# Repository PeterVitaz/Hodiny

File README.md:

# Hodiny v4.6

Author:     Peter Vitaz
email:      peter@vitaz.tv

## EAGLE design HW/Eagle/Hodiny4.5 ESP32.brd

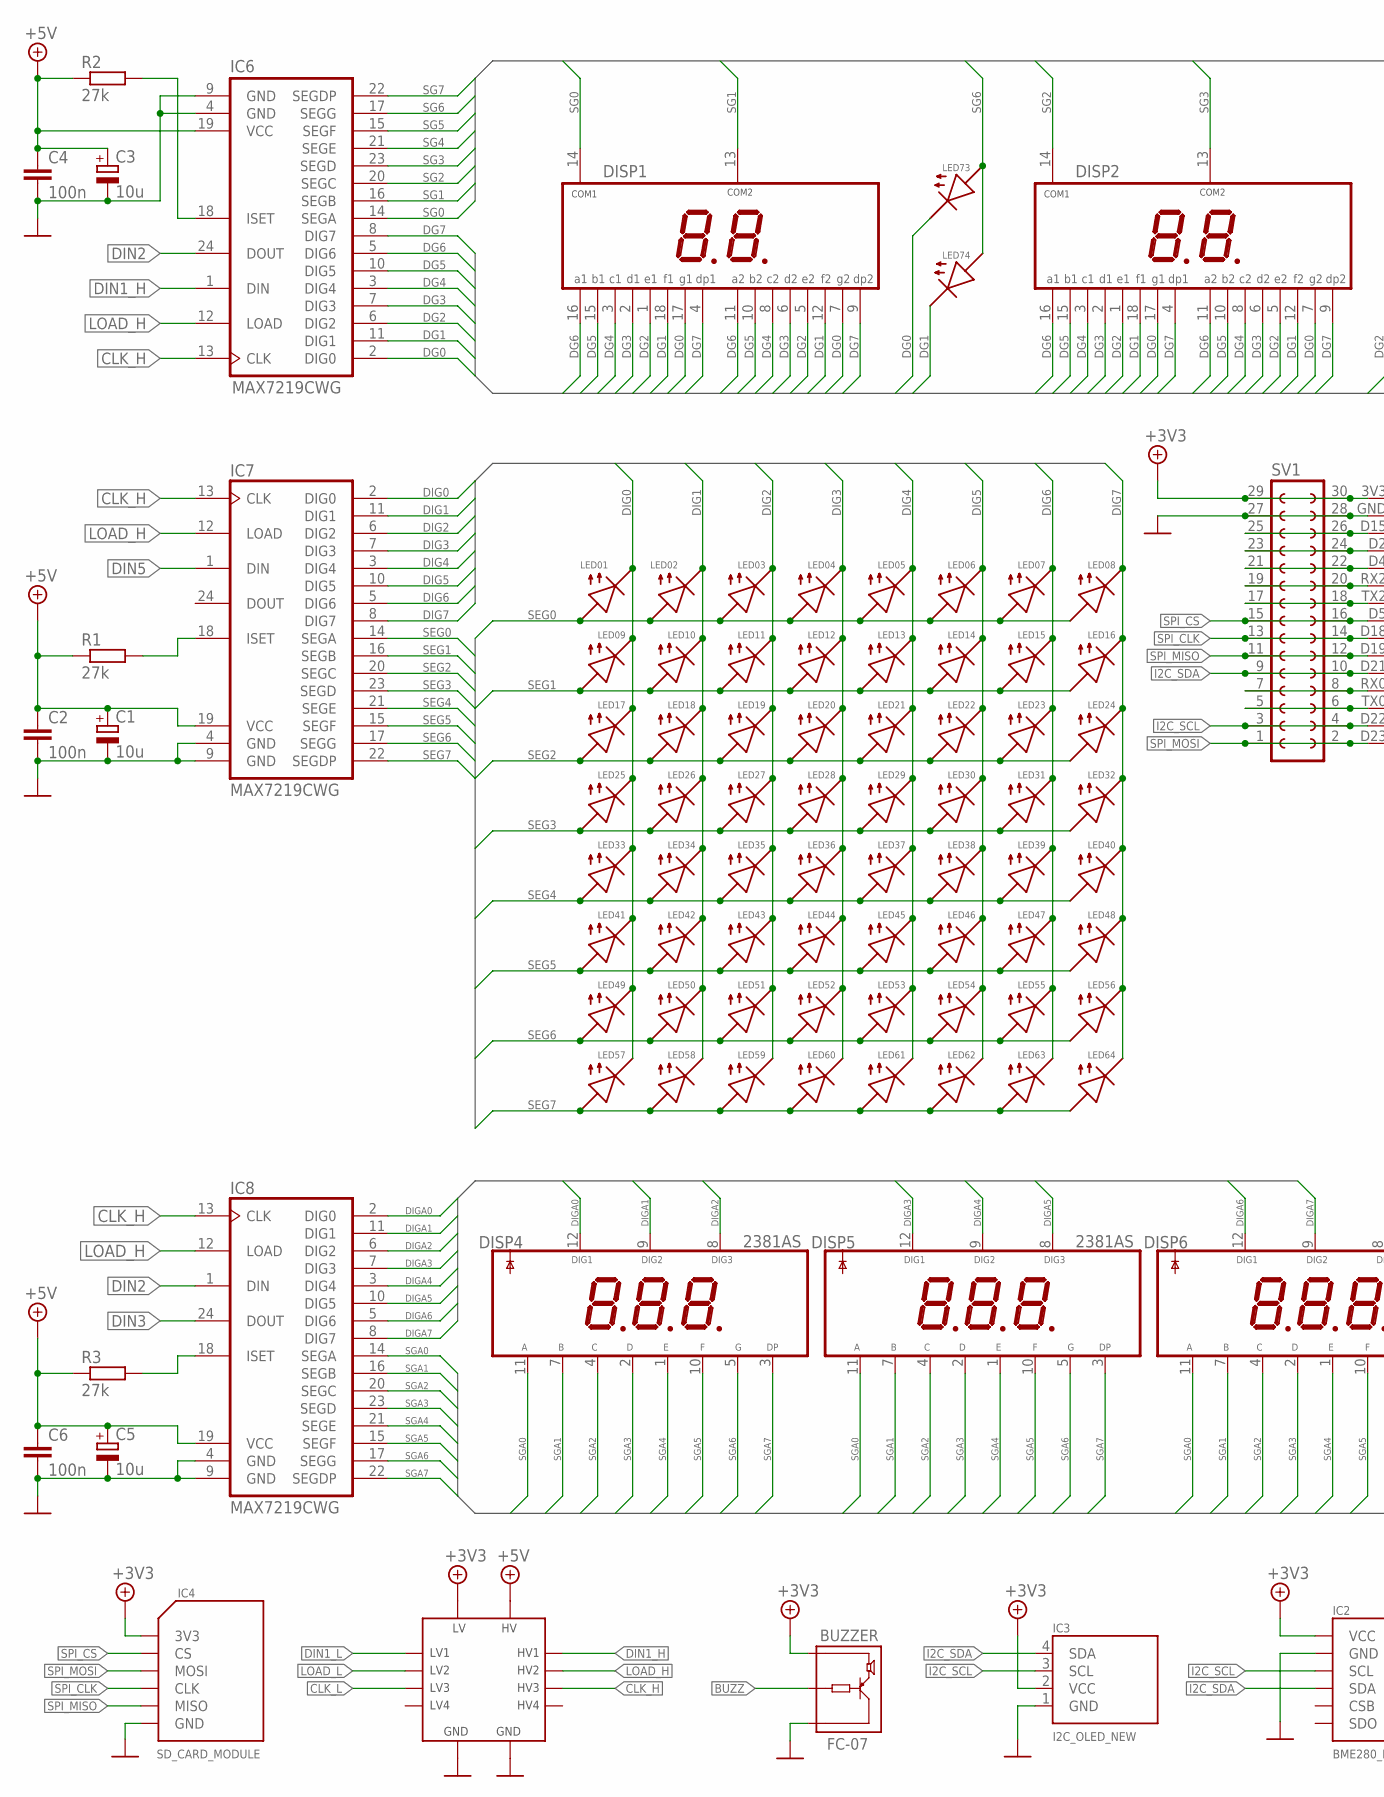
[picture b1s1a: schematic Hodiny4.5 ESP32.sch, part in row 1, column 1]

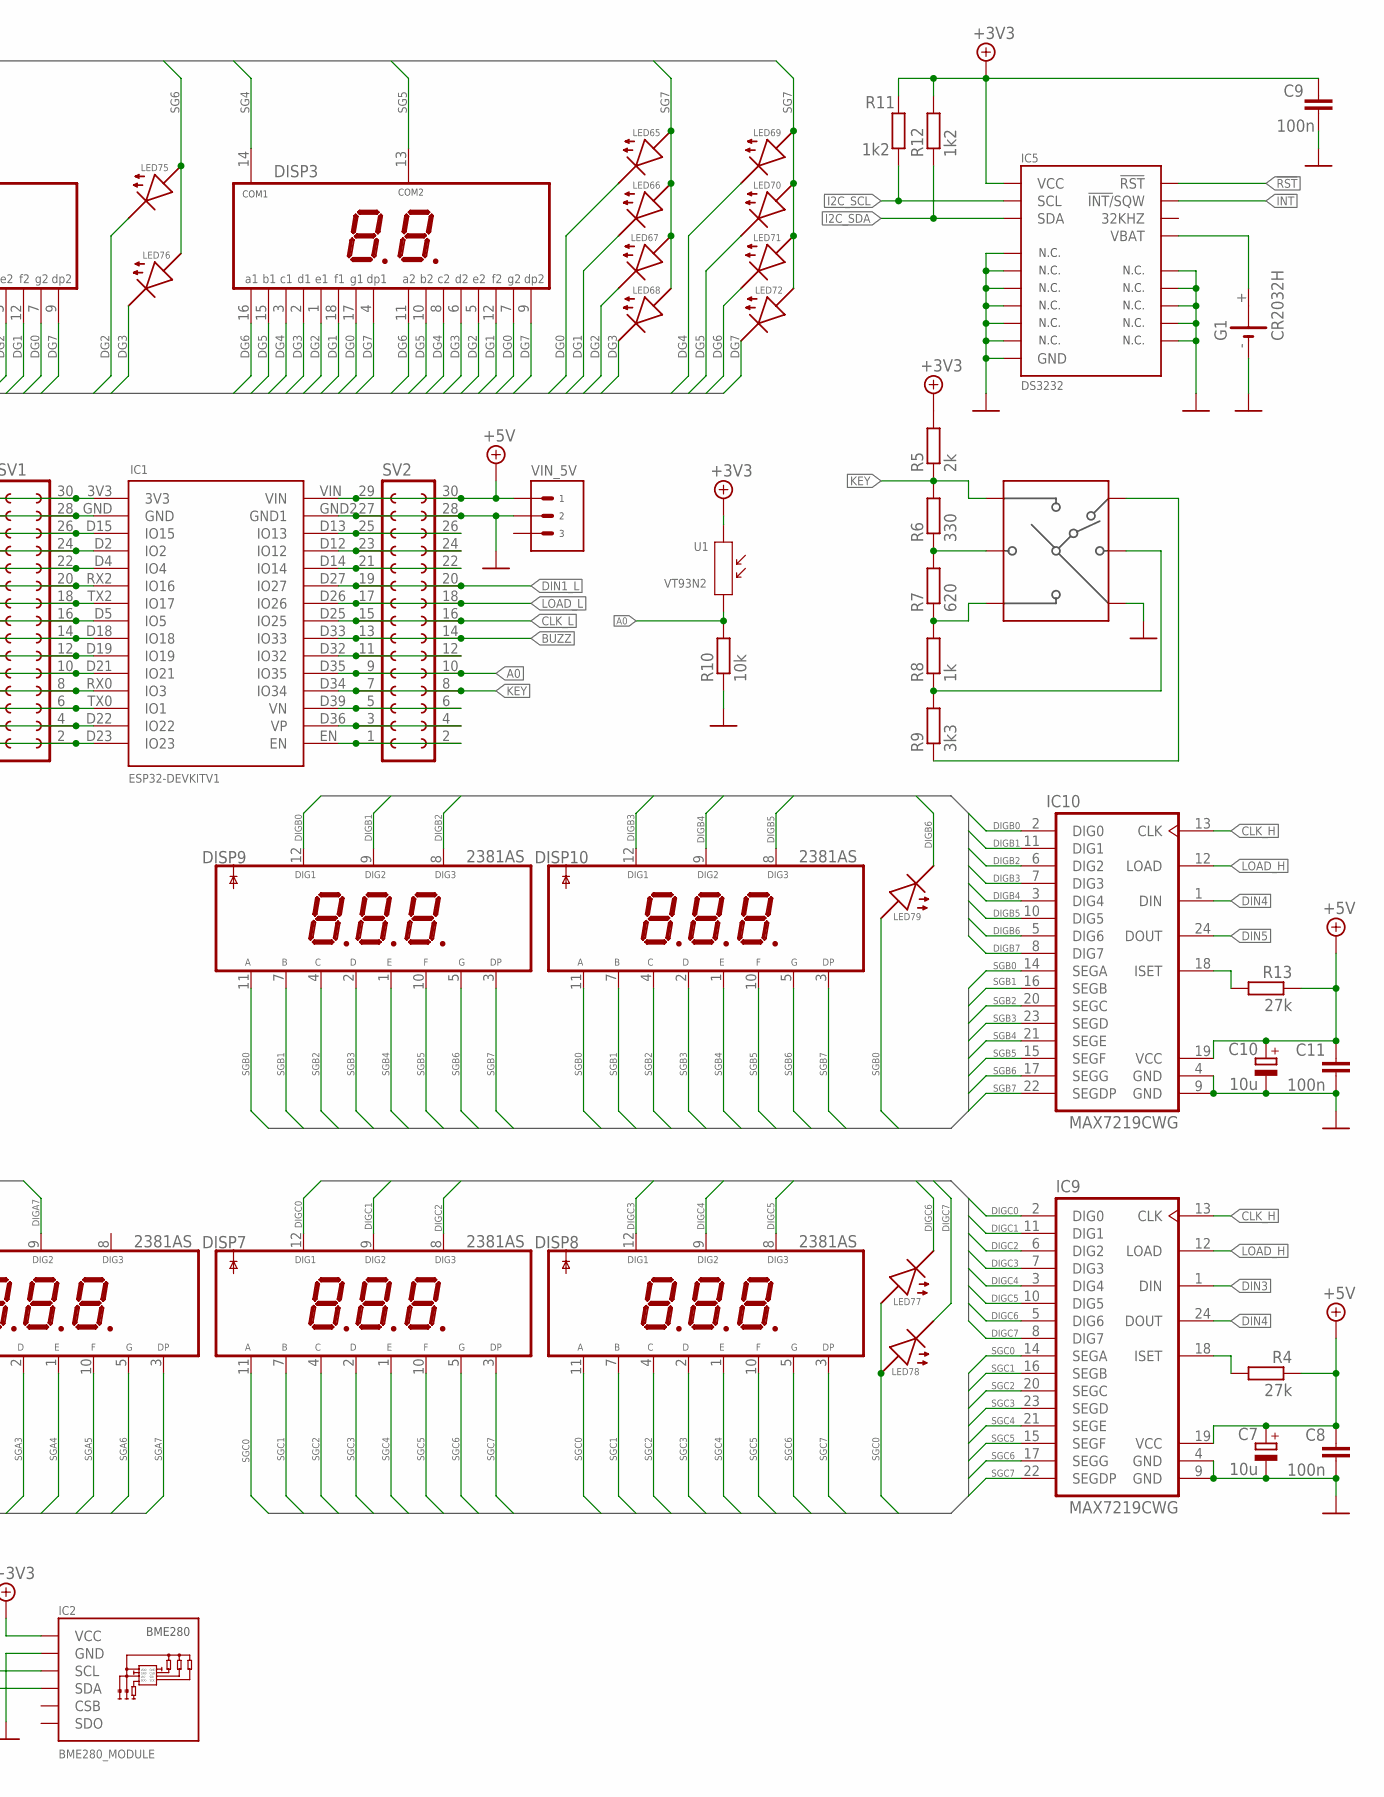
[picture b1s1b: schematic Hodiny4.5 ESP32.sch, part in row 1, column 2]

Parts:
C1, C3, C5, C7, C10: 10u; E2,5-5
C2, C4, C6, C8, C9, C11: 100n; C050-024X044
DISP1, DISP2, DISP3: DA08-11; DA08-11EWA
DISP4, DISP5, DISP6, DISP7, DISP8, DISP9, DISP10: 2381AS
G1: CR2032H
IC1: ESP32DEVKITV1NEW; ESP32-DEVKITV1A
IC2: BME280_MODULE
IC3: I2C_OLED_NEW; I2C_OLED_PACKAGE
IC4: SD_CARD_MODULE; SD_CARD
IC5: DS3232; SO20L
IC6, IC7, IC8, IC9, IC10: MAX7219CWG; SO24L
LED01, LED02, LED03, LED04, LED05, LED06, LED07, LED08, LED09, LED10, LED11, LED12, LED13, LED14, LED15, LED16, LED17, LED18, LED19, LED20, LED21, LED22, LED23, LED24, LED25, LED26, LED27, LED28, LED29, LED30, LED31, LED32, LED33, LED34, LED35, LED36, LED37, LED38, LED39, LED40, LED41, LED42, LED43, LED44, LED45, LED46, LED47, LED48, LED49, LED50, LED51, LED52, LED53, LED54, LED55, LED56, LED57, LED58, LED59, LED60, LED61, LED62, LED63, LED64, LED65, LED66, LED67, LED68, LED69, LED70, LED71, LED72, LED73, LED74, LED75, LED76, LED77, LED78, LED79: LED_45; LED3MM
LEVEL_SHIFTER: LEVEL_SHIFTER_4; LVS_4
R1, R2, R3, R4, R13: 27k; 0207/10
R5: 2k; 0207/10
R6: 330; 0207/10
R7: 620; 0207/10
R8: 1k; 0207/10
R9: 3k3; 0207/10
R10: 10k; 0207/10
R11, R12: 1k2; 0207/10
SV1, SV2: FE15-2
SWITCH: 5-WAY-SWITCH
U1: VT93N2; SNR2-3.0
U$2: BUZZER_FC-07; BUZZER
VIN_5V: 22-27-2031-03; 6410-03

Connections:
3V3: C9.1, IC1.3V3, IC2.VCC, IC3.2 (VCC), IC4.3V3, IC5.4 (VCC), LEVEL_SHIFTER.3 (LV), R5.2, R11.2, R12.2, SV1.29, SV1.30, U1.1, U$2.VCC
!INT: IC5.5 (!INT/!SQW)
!RST: IC5.6 (!RST)
+5V: C1.+, C2.1, C3.+, C4.1, C5.+, C6.1, C7.+, C8.1, C10.+, C11.1, IC1.VIN, IC6.19 (VCC), IC7.19 (VCC), IC8.19 (VCC), IC9.19 (VCC), IC10.19 (VCC), LEVEL_SHIFTER.10 (HV), R1.1, R2.1, R3.1, R4.1, R13.1, SV2.29, SV2.30, VIN_5V.1 (-1)
A0: IC1.D35 (IO35), R10.2, SV2.9, SV2.10, U1.2
BUZZ: IC1.D33 (IO33), SV2.13, SV2.14, U$2.IO (IN)
CLK_H: IC6.13 (CLK), IC7.13 (CLK), IC8.13 (CLK), IC9.13 (CLK), IC10.13 (CLK), LEVEL_SHIFTER.8 (HV3)
CLK_L: IC1.D25 (IO25), LEVEL_SHIFTER.5 (LV3), SV2.15, SV2.16
DG0: DISP1.7 (G2), DISP1.17 (G1), DISP2.7 (G2), DISP2.17 (G1), DISP3.7 (G2), DISP3.17 (G1), IC6.2 (DIG0), LED65.K (C), LED73.K (C)
DG1: DISP1.12 (F2), DISP1.18 (F1), DISP2.12 (F2), DISP2.18 (F1), DISP3.12 (F2), DISP3.18 (F1), IC6.11 (DIG1), LED66.K (C), LED74.K (C)
DG2: DISP1.1 (E1), DISP1.5 (E2), DISP2.1 (E1), DISP2.5 (E2), DISP3.1 (E1), DISP3.5 (E2), IC6.6 (DIG2), LED67.K (C), LED75.K (C)
DG3: DISP1.2 (D1), DISP1.6 (D2), DISP2.2 (D1), DISP2.6 (D2), DISP3.2 (D1), DISP3.6 (D2), IC6.7 (DIG3), LED68.K (C), LED76.K (C)
DG4: DISP1.3 (C1), DISP1.8 (C2), DISP2.3 (C1), DISP2.8 (C2), DISP3.3 (C1), DISP3.8 (C2), IC6.3 (DIG4), LED69.K (C)
DG5: DISP1.10 (B2), DISP1.15 (B1), DISP2.10 (B2), DISP2.15 (B1), DISP3.10 (B2), DISP3.15 (B1), IC6.10 (DIG5), LED70.K (C)
DG6: DISP1.11 (A2), DISP1.16 (A1), DISP2.11 (A2), DISP2.16 (A1), DISP3.11 (A2), DISP3.16 (A1), IC6.5 (DIG6), LED71.K (C)
DG7: DISP1.4 (DP1), DISP1.9 (DP2), DISP2.4 (DP1), DISP2.9 (DP2), DISP3.4 (DP1), DISP3.9 (DP2), IC6.8 (DIG7), LED72.K (C)
DIG0: IC7.2 (DIG0), LED01.K (C), LED09.K (C), LED17.K (C), LED25.K (C), LED33.K (C), LED41.K (C), LED49.K (C), LED57.K (C)
DIG1: IC7.11 (DIG1), LED02.K (C), LED10.K (C), LED18.K (C), LED26.K (C), LED34.K (C), LED42.K (C), LED50.K (C), LED58.K (C)
DIG2: IC7.6 (DIG2), LED03.K (C), LED11.K (C), LED19.K (C), LED27.K (C), LED35.K (C), LED43.K (C), LED51.K (C), LED59.K (C)
DIG3: IC7.7 (DIG3), LED04.K (C), LED12.K (C), LED20.K (C), LED28.K (C), LED36.K (C), LED44.K (C), LED52.K (C), LED60.K (C)
DIG4: IC7.3 (DIG4), LED05.K (C), LED13.K (C), LED21.K (C), LED29.K (C), LED37.K (C), LED45.K (C), LED53.K (C), LED61.K (C)
DIG5: IC7.10 (DIG5), LED06.K (C), LED14.K (C), LED22.K (C), LED30.K (C), LED38.K (C), LED46.K (C), LED54.K (C), LED62.K (C)
DIG6: IC7.5 (DIG6), LED07.K (C), LED15.K (C), LED23.K (C), LED31.K (C), LED39.K (C), LED47.K (C), LED55.K (C), LED63.K (C)
DIG7: IC7.8 (DIG7), LED08.K (C), LED16.K (C), LED24.K (C), LED32.K (C), LED40.K (C), LED48.K (C), LED56.K (C), LED64.K (C)
DIGA0: DISP4.12 (DIG1), IC8.2 (DIG0)
DIGA1: DISP4.9 (DIG2), IC8.11 (DIG1)
DIGA2: DISP4.8 (DIG3), IC8.6 (DIG2)
DIGA3: DISP5.12 (DIG1), IC8.7 (DIG3)
DIGA4: DISP5.9 (DIG2), IC8.3 (DIG4)
DIGA5: DISP5.8 (DIG3), IC8.10 (DIG5)
DIGA6: DISP6.12 (DIG1), IC8.5 (DIG6)
DIGA7: DISP6.9 (DIG2), IC8.8 (DIG7)
DIGB0: DISP9.12 (DIG1), IC10.2 (DIG0)
DIGB1: DISP9.9 (DIG2), IC10.11 (DIG1)
DIGB2: DISP9.8 (DIG3), IC10.6 (DIG2)
DIGB3: DISP10.12 (DIG1), IC10.7 (DIG3)
DIGB4: DISP10.9 (DIG2), IC10.3 (DIG4)
DIGB5: DISP10.8 (DIG3), IC10.10 (DIG5)
DIGB6: IC10.5 (DIG6), LED79.K (C)
DIGB7: IC10.8 (DIG7)
DIGC0: DISP7.12 (DIG1), IC9.2 (DIG0)
DIGC1: DISP7.9 (DIG2), IC9.11 (DIG1)
DIGC2: DISP7.8 (DIG3), IC9.6 (DIG2)
DIGC3: DISP8.12 (DIG1), IC9.7 (DIG3)
DIGC4: DISP8.9 (DIG2), IC9.3 (DIG4)
DIGC5: DISP8.8 (DIG3), IC9.10 (DIG5)
DIGC6: IC9.5 (DIG6), LED77.K (C)
DIGC7: IC9.8 (DIG7), LED78.K (C)
DIN1_H: IC6.1 (DIN), LEVEL_SHIFTER.12 (HV1)
DIN1_L: IC1.D27 (IO27), LEVEL_SHIFTER.1 (LV1), SV2.19, SV2.20
DIN2: IC6.24 (DOUT), IC8.1 (DIN)
DIN3: IC8.24 (DOUT), IC9.1 (DIN)
DIN4: IC9.24 (DOUT), IC10.1 (DIN)
DIN5: IC7.1 (DIN), IC10.24 (DOUT)
GND: C1.-, C2.2, C3.-, C4.2, C5.-, C6.2, C7.-, C8.2, C9.2, C10.-, C11.2, G1.-, IC1.GND, IC1.GND2 (GND1), IC2.GND, IC3.1 (GND), IC4.GND, IC5.1 (N.C._1), IC5.2 (N.C._2), IC5.7 (N.C._3), IC5.8 (N.C._4), IC5.9 (N.C._5), IC5.10 (N.C._6), IC5.11 (N.C._7), IC5.12 (N.C._8), IC5.13 (N.C._9), IC5.14 (N.C._10), IC5.15 (GND), IC5.19 (N.C._11), IC6.4 (GND), IC6.9 (GND), IC7.4 (GND), IC7.9 (GND), IC8.4 (GND), IC8.9 (GND), IC9.4 (GND), IC9.9 (GND), IC10.4 (GND), IC10.9 (GND), LEVEL_SHIFTER.4 (GNDL), LEVEL_SHIFTER.9 (GNDH), R10.1, SV1.27, SV1.28, SV2.27, SV2.28, SWITCH.4, U$2.GND, VIN_5V.2 (-2)
I2C_SCL: IC1.D22 (IO22), IC2.SCL, IC3.3 (SCL), IC5.18 (SCL), IC5.20 (SCL), R11.1, SV1.3, SV1.4
I2C_SDA: IC1.D21 (IO21), IC2.SDA, IC3.4 (SDA), IC5.17 (SDA), R12.1, SV1.9, SV1.10
KEY: IC1.D34 (IO34), R5.1, R6.2, SV2.7, SV2.8, SWITCH.1
LOAD_H: IC6.12 (LOAD), IC7.12 (LOAD), IC8.12 (LOAD), IC9.12 (LOAD), IC10.12 (LOAD), LEVEL_SHIFTER.11 (HV2)
LOAD_L: IC1.D26 (IO26), LEVEL_SHIFTER.2 (LV2), SV2.17, SV2.18
unnamed: IC6.18 (ISET), R2.2
unnamed: IC7.18 (ISET), R1.2
unnamed: IC8.18 (ISET), R3.2
unnamed: IC9.18 (ISET), R4.2
unnamed: G1.+, IC5.16 (VBAT)
unnamed: IC10.18 (ISET), R13.2
unnamed: IC1.D4 (IO4), SV1.21, SV1.22
unnamed: R6.1, R7.2, SWITCH.2
unnamed: R7.1, R8.2, SWITCH.3
unnamed: R8.1, R9.2, SWITCH.5
unnamed: R9.1, SWITCH.6
unnamed: IC1.D15 (IO15), SV1.25, SV1.26
unnamed: IC1.TX2 (IO17), SV1.17, SV1.18
unnamed: IC1.RX0 (IO3), SV1.7, SV1.8
unnamed: IC1.TX0 (IO1), SV1.5, SV1.6
unnamed: IC1.D13 (IO13), SV2.25, SV2.26
unnamed: IC1.D12 (IO12), SV2.23, SV2.24
unnamed: IC1.D14 (IO14), SV2.21, SV2.22
unnamed: IC1.D32 (IO32), SV2.11, SV2.12
unnamed: IC1.D39 (VN), SV2.5, SV2.6
unnamed: IC1.D36 (VP), SV2.3, SV2.4
unnamed: IC1.EN, SV2.1, SV2.2
RX2: IC1.RX2 (IO16), SV1.19, SV1.20
SEG0: IC7.14 (SEGA), LED01.A, LED02.A, LED03.A, LED04.A, LED05.A, LED06.A, LED07.A, LED08.A
SEG1: IC7.16 (SEGB), LED09.A, LED10.A, LED11.A, LED12.A, LED13.A, LED14.A, LED15.A, LED16.A
SEG2: IC7.20 (SEGC), LED17.A, LED18.A, LED19.A, LED20.A, LED21.A, LED22.A, LED23.A, LED24.A
SEG3: IC7.23 (SEGD), LED25.A, LED26.A, LED27.A, LED28.A, LED29.A, LED30.A, LED31.A, LED32.A
SEG4: IC7.21 (SEGE), LED33.A, LED34.A, LED35.A, LED36.A, LED37.A, LED38.A, LED39.A, LED40.A
SEG5: IC7.15 (SEGF), LED41.A, LED42.A, LED43.A, LED44.A, LED45.A, LED46.A, LED47.A, LED48.A
SEG6: IC7.17 (SEGG), LED49.A, LED50.A, LED51.A, LED52.A, LED53.A, LED54.A, LED55.A, LED56.A
SEG7: IC7.22 (SEGDP), LED57.A, LED58.A, LED59.A, LED60.A, LED61.A, LED62.A, LED63.A, LED64.A
SG0: DISP1.14 (COM1), IC6.14 (SEGA)
SG1: DISP1.13 (COM2), IC6.16 (SEGB)
SG2: DISP2.14 (COM1), IC6.20 (SEGC)
SG3: DISP2.13 (COM2), IC6.23 (SEGD)
SG4: DISP3.14 (COM1), IC6.21 (SEGE)
SG5: DISP3.13 (COM2), IC6.15 (SEGF)
SG6: IC6.17 (SEGG), LED73.A, LED74.A, LED75.A, LED76.A
SG7: IC6.22 (SEGDP), LED65.A, LED66.A, LED67.A, LED68.A, LED69.A, LED70.A, LED71.A, LED72.A
SGA0: DISP4.11 (A), DISP5.11 (A), DISP6.11 (A), IC8.14 (SEGA)
SGA1: DISP4.7 (B), DISP5.7 (B), DISP6.7 (B), IC8.16 (SEGB)
SGA2: DISP4.4 (C), DISP5.4 (C), DISP6.4 (C), IC8.20 (SEGC)
SGA3: DISP4.2 (D), DISP5.2 (D), DISP6.2 (D), IC8.23 (SEGD)
SGA4: DISP4.1 (E), DISP5.1 (E), DISP6.1 (E), IC8.21 (SEGE)
SGA5: DISP4.10 (F), DISP5.10 (F), DISP6.10 (F), IC8.15 (SEGF)
SGA6: DISP4.5 (G), DISP5.5 (G), DISP6.5 (G), IC8.17 (SEGG)
SGA7: DISP4.3 (DP), DISP5.3 (DP), DISP6.3 (DP), IC8.22 (SEGDP)
SGB0: DISP9.11 (A), DISP10.11 (A), IC10.14 (SEGA), LED79.A
SGB1: DISP9.7 (B), DISP10.7 (B), IC10.16 (SEGB)
SGB2: DISP9.4 (C), DISP10.4 (C), IC10.20 (SEGC)
SGB3: DISP9.2 (D), DISP10.2 (D), IC10.23 (SEGD)
SGB4: DISP9.1 (E), DISP10.1 (E), IC10.21 (SEGE)
SGB5: DISP9.10 (F), DISP10.10 (F), IC10.15 (SEGF)
SGB6: DISP9.5 (G), DISP10.5 (G), IC10.17 (SEGG)
SGB7: DISP9.3 (DP), DISP10.3 (DP), IC10.22 (SEGDP)
SGC0: DISP7.11 (A), DISP8.11 (A), IC9.14 (SEGA), LED77.A, LED78.A
SGC1: DISP7.7 (B), DISP8.7 (B), IC9.16 (SEGB)
SGC2: DISP7.4 (C), DISP8.4 (C), IC9.20 (SEGC)
SGC3: DISP7.2 (D), DISP8.2 (D), IC9.23 (SEGD)
SGC4: DISP7.1 (E), DISP8.1 (E), IC9.21 (SEGE)
SGC5: DISP7.10 (F), DISP8.10 (F), IC9.15 (SEGF)
SGC6: DISP7.5 (G), DISP8.5 (G), IC9.17 (SEGG)
SGC7: DISP7.3 (DP), DISP8.3 (DP), IC9.22 (SEGDP)
SPI_CLK: IC1.D18 (IO18), IC4.CLK, SV1.13, SV1.14
SPI_CS: IC1.D5 (IO5), IC4.CS, SV1.15, SV1.16
SPI_MISO: IC1.D19 (IO19), IC4.MISO, SV1.11, SV1.12
SPI_MOSI: IC1.D23 (IO23), IC4.MOSI, SV1.1, SV1.2
XX: IC1.D2 (IO2), SV1.23, SV1.24

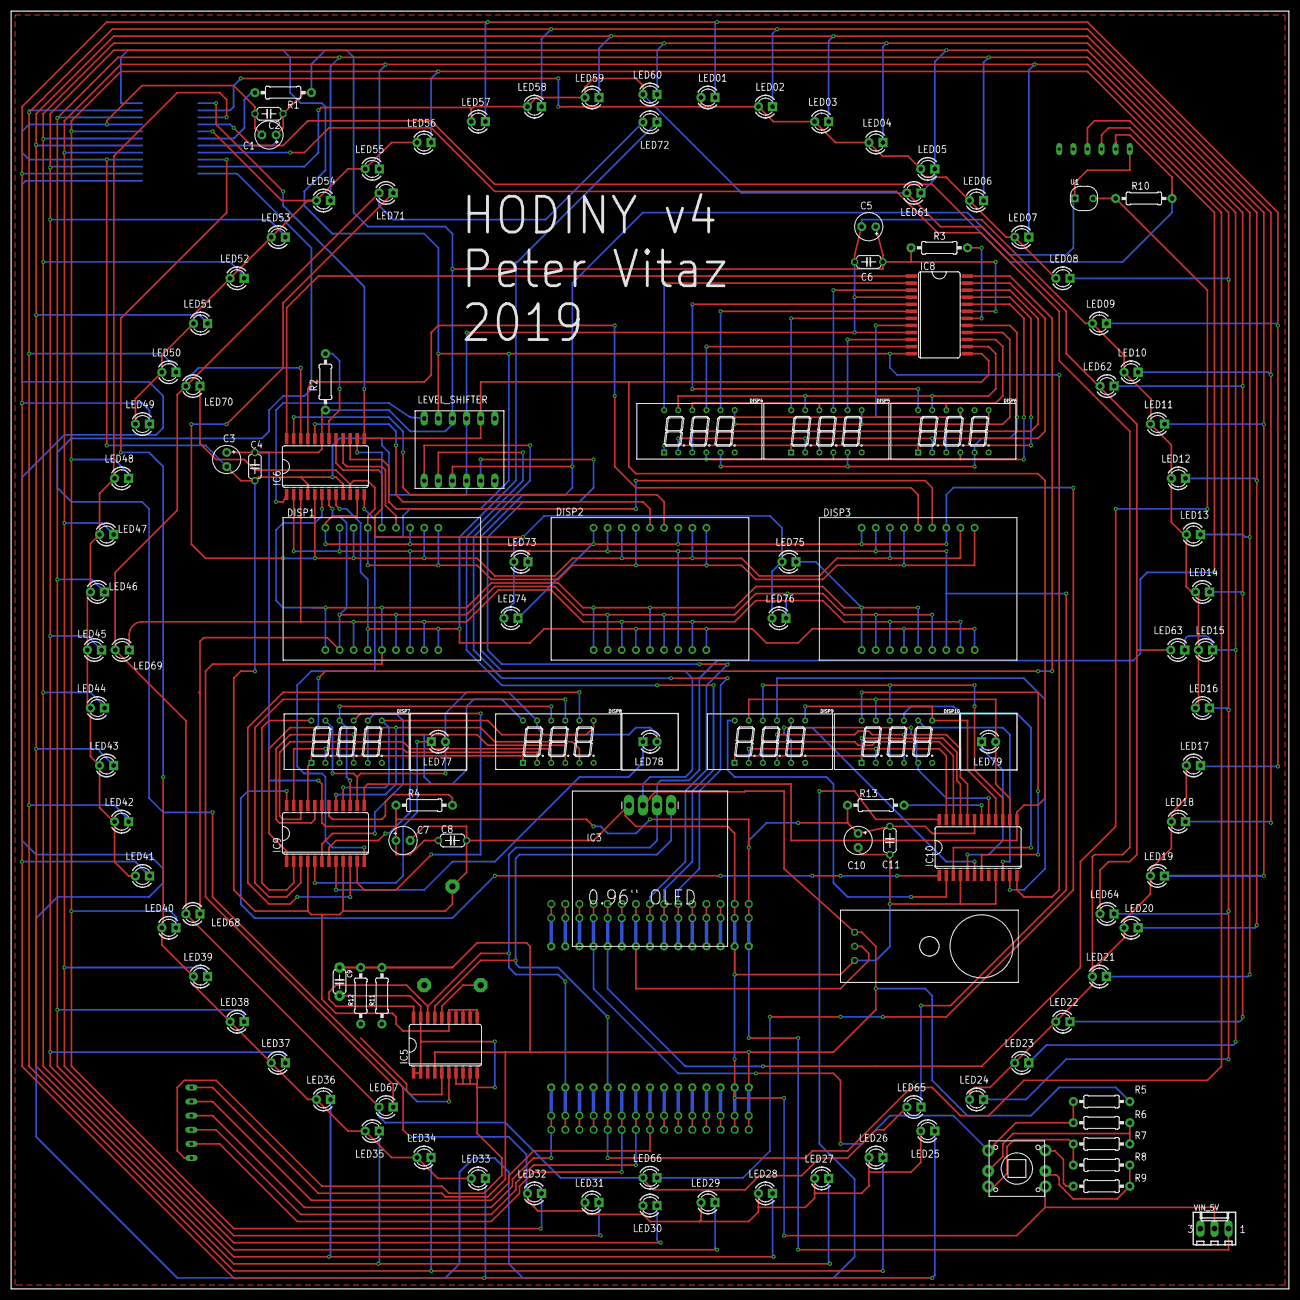
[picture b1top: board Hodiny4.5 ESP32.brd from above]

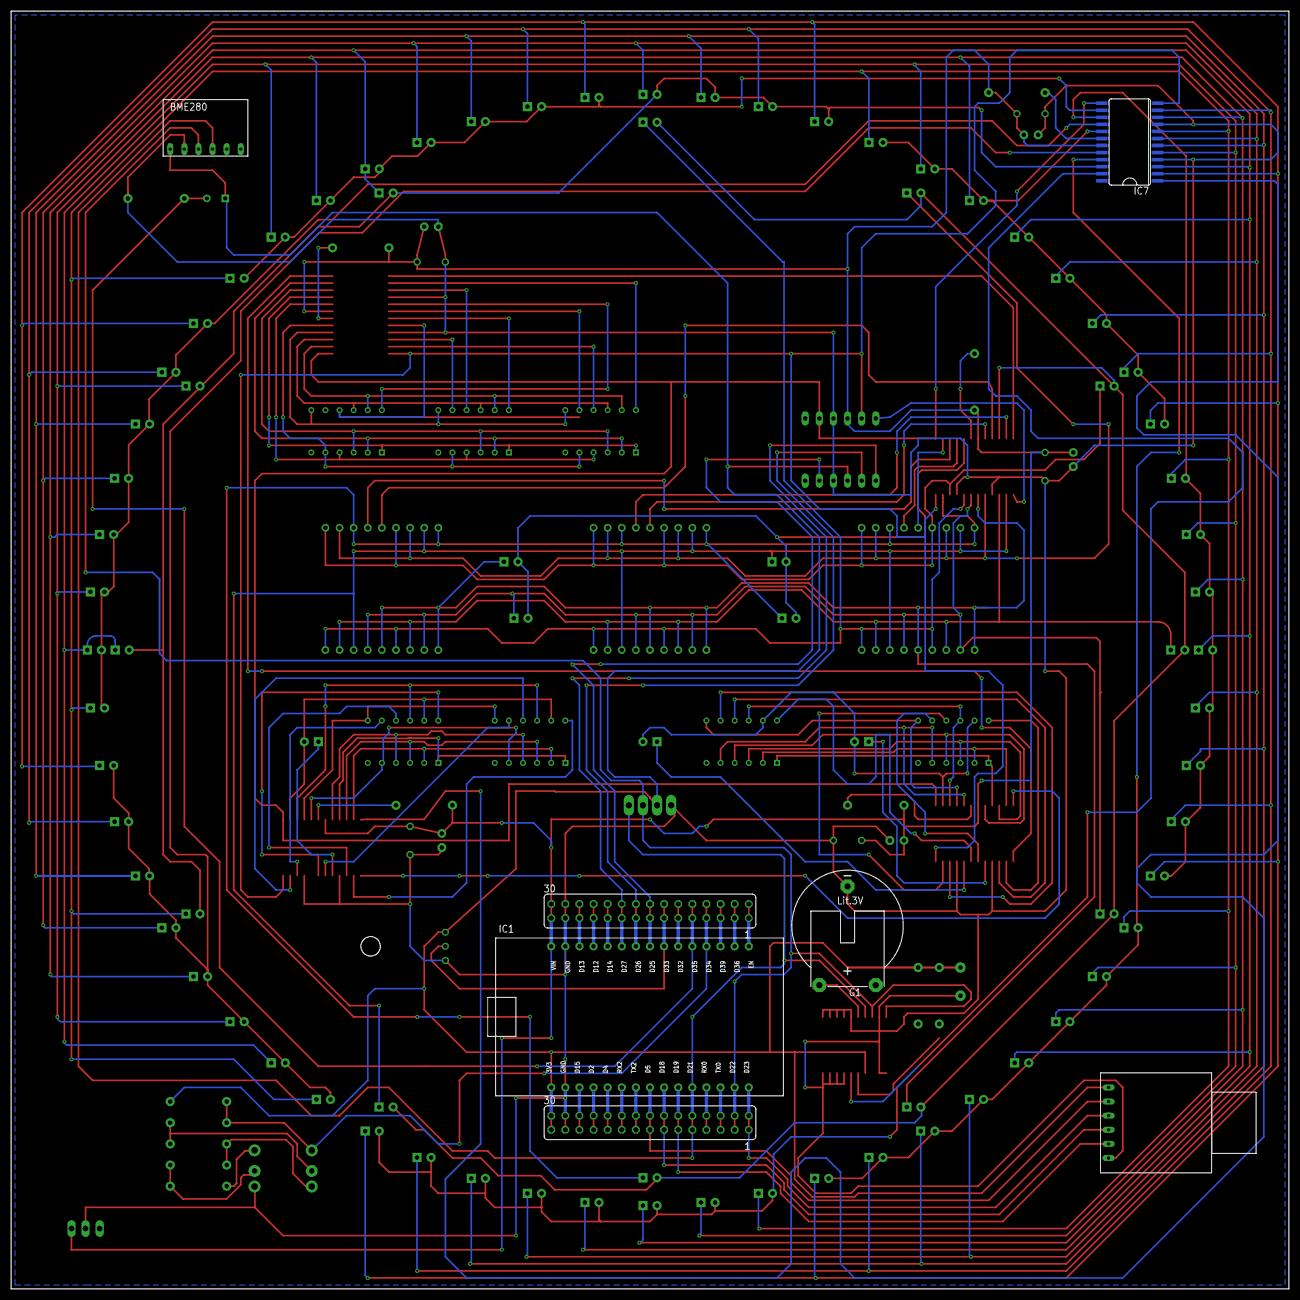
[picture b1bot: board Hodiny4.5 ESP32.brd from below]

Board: 2 copper layers, 230.0 x 230.0 mm, 131 parts (7 on the bottom side), 125 nets.

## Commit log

2024-03-22 Adding Eagle sch and pcb file to the HW folder
2024-03-22 Add old projects files and libraries
2024-03-22 Create PlatformIO project
2024-03-22 Reading from SD card finished
2024-03-22 Connecting to the internet works
2024-03-24 Oled works. Used U8g8 lib. Work as terminal.
2024-03-24 Add .pio folder to the git
2024-03-24 Get time to int hours, minutes, seconds
2024-03-24 Adding LedControl lib
2024-03-24 Working LED Hours and Ring
2024-03-25 Working Button
2024-03-25 Update Time NTP when button is released
2024-04-02 Add Timezone and Daylight Saving Time
2024-04-15 Add update time at 23:59:00
